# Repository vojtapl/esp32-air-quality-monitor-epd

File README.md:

<h1 align="center">
    
</h1>

# SEN66 Air Quality Monitor With EPD Output

The goal of this project is to create portable air quality monitor, which can be
used to measure the air quality in all environments I am in throughout the day,
especially where I sleep. Some sample measurements available
[here](/software/sample%20data/README.md).

## Readme if you Consider Making This

I would like make a new hardware and accompanying software revision, as I have
found some design quirks I have made:

- I have accidentally bought BWR EPD instead of the newer BWRY, forcing me to
  not be able to use the yellow color.
- The power button is sunken too much (by about 1 mm).
- The rotary encoder is not a good user interface, as the EPD has a refresh time
  of about 15 seconds (though the BWRY version may improve this); dedicated
  buttons would be better.
- The cable to the SEN66 sensor is quite finicky to make without the proper
  tools.
- Looking at the SEN66 sensor itself, it is of a very nice form factor, though
  not that good price-wise.

## To-Do:

- Add photos, features, and description.
- Beautify the code.
- Check the accuracy displayed.
- Record and add some data on Git.
- Clear display of current values with _badness level_.
- Show trend in overview.
- Consider adding AP functionality.
- Consider using bat_low alarm.
- Consider adding red background to really bad values.
- Add average overview.
- Optimize the power consumption.

### To-Do for Next Revision(s)

- Consider adding soft power button.
- Consider adding a _busy_ LED if the BWRY EPD still has slow update time.
- Create a version without battery.

## Build Instructions

### Required parts:

- 1x M3x(3-5) mm grub screw
- 3x M3x(15-25) mm screw with countersunk head
- 3x M3 thread inserts suitable for a 4 mm hole
- micro SD card for data storage and graphing function
- 0.5 mm plastic sheet cut to 37 mm x 73 mm as a protection for the EPD (though
  with a little modification to the case files can be disregarded)
- populated PCB with a cap for the power switch
- printed case, encoder knob and a gasket for SEN66 (recommended to be made with
  a flexible plastic; not required)
- SEN66 - PCB connection wire
- 18650 battery, if non-powered usage is desired

### Some Photos Which Should Help

<h3 align="center">
    
</h3>
<h3 align="center">
    
</h3>
<h3 align="center">
    
</h3>
<h3 align="center">
    
</h3>

## Air Quality Thresholds Table

|                                | PM2.5, PM1, PM4 | PM10       | humidex  | voc, nox index | CO2          |
| ------------------------------ | --------------- | ---------- | -------- | -------------- | ------------ |
| good                           | [0; 9]          | [0; 55]    | [0; 28]  | [0; 50]        | [400; 800]   |
| moderate                       | (9; 35.5]       | (55; 155]  | (28; 32] | (50; 100]      | (800; 1000]  |
| unhealthy for sensitive groups | (35.5; 55.5]    | (155; 255] | (32; 36] | (100; 200]     | (1000; 1500] |
| unhealthy                      | (55.5; 125.5]   | (255; 355] | (36; 42] | (200; 300]     | (1500; 2000] |
| very unhealhty                 | (125.5; 225.5]  | (355; 425] | (42; 45] | (300; 400]     | (2000; 5000] |
| hazardous                      | (225.5; ∞]      | (425; ∞]   | (45; ∞)  | (400; ∞)       | (5000; ∞)    |

Based on:

- [Agency for Toxic Substances and Disease Registry (ATSDR). 2024. Guidance for Inhalation Exposures to Particulate Matter. U.S. Department of Health and Human Services, Public Health Service, Atlanta, GA. June 2024 update, Appendix B](https://www.atsdr.cdc.gov/pha-guidance/resources/ATSDR-Particulate-Matter-Guidance-508.pdf)
  for PM2.5 (and from it PM1 and PM4 as there do not seem to be any specific
  resources for these) and PM10
- [XIRIS. "Environmental and Indoor Measuring." XIRIS, https://www.xiris.si/en/projects/environmental-and-indoor-measuring/. Accessed 1 Aug. 2025](https://www.xiris.si/en/projects/environmental-and-indoor-measuring/)
  for CO2 with lowered good and moderate levels
- [Environment and Climate Change Canada. (n.d.). Warm season weather hazards. Government of Canada. Retrieved August 1, 2025, from https://www.canada.ca/en/environment-climate-change/services/seasonal-weather-hazards/warm-season-weather-hazards.html#toc7](https://www.canada.ca/en/environment-climate-change/services/seasonal-weather-hazards/warm-season-weather-hazards.html#toc7)
  for humidex
- The VOC and NOX indices are not based on anything as I have not found any good
  interpretation help in SEN66's docs. From my measurements the NOX usually
  hovers in the range [0; 2] and VOC jumps semi randomly. I would like to
  investigate these values more in the future.

## Attributions

- The SD card, Wi-Fi and battery icons are made by Gaai available at
  [lopaka](https://github.com/sbrin/lopaka).
- The font used for the charging status markings on the case is Atkinson
  Hyperlegible, available at
  [Braille Institute's website](https://www.brailleinstitute.org/freefont/)
- The SD card abstraction functions are based on
  [this example](https://github.com/espressif/arduino-esp32/blob/master/libraries/SD_MMC/examples/SDMMC_Test/SDMMC_Test.ino).

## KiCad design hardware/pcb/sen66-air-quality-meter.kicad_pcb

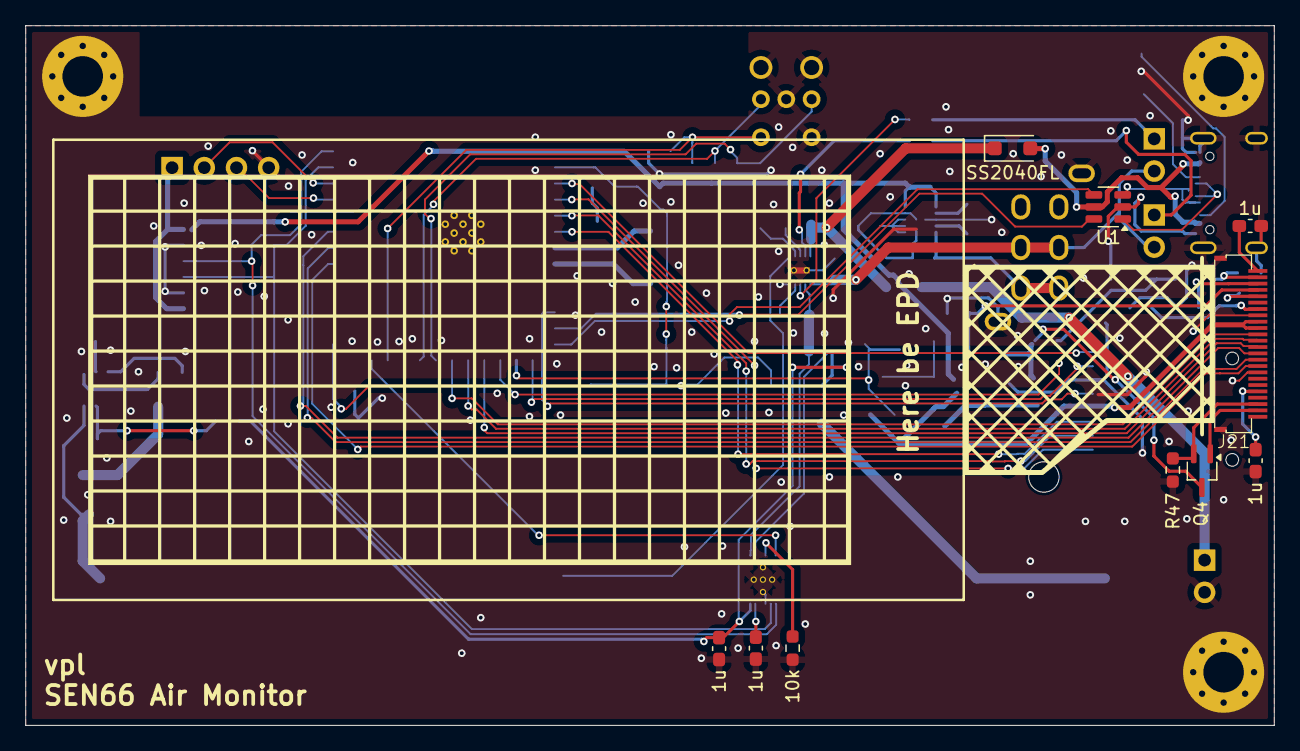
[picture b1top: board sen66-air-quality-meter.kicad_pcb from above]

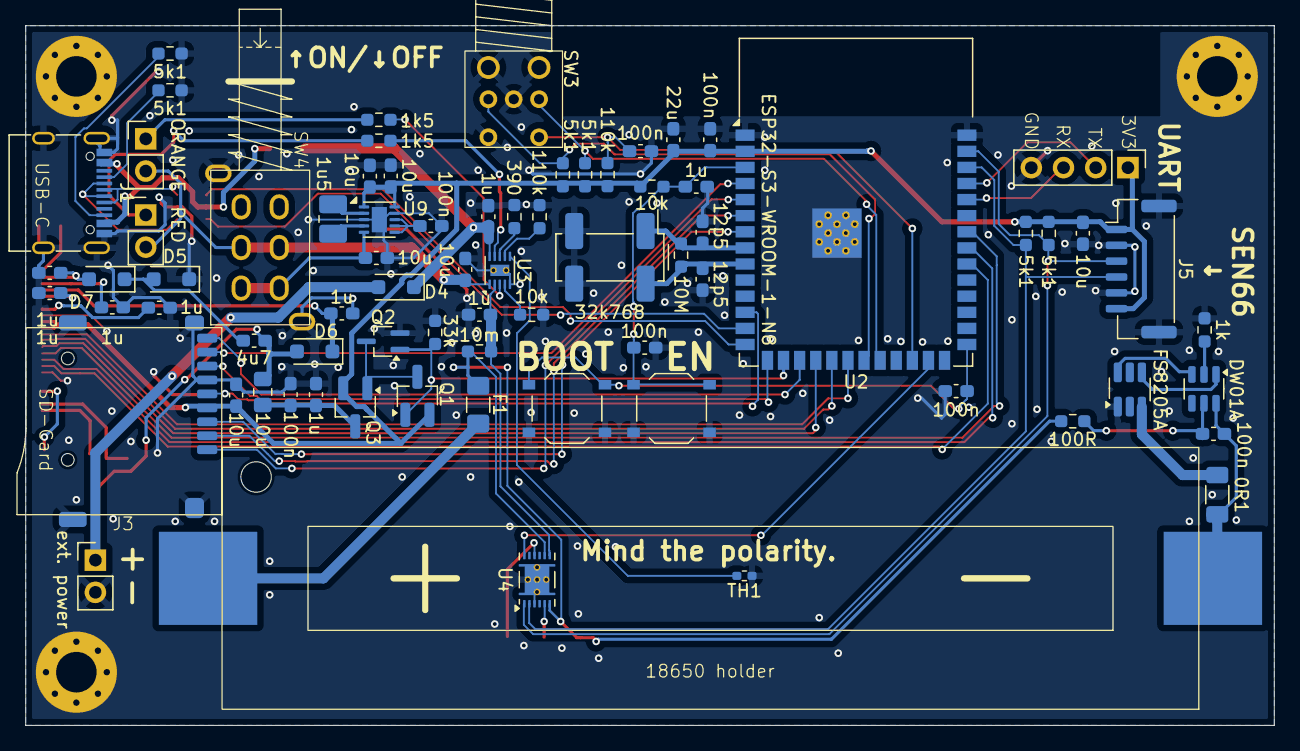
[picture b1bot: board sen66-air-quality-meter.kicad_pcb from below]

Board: 2 copper layers, 98.5 x 55.2 mm, 88 parts (75 on the bottom side), 74 nets.

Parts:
BT1: 18650 battery holder; BH-18650-B1BA002
C1, C2, C6, C8, C15, C26, C28: 100n; C_0603_1608Metric_Pad1.08x0.95mm_HandSolder
C3, C7, C10, C14, C16, C17, C19, C20, C21, C22, C23, C24, C25: 1u; C_0603_1608Metric_Pad1.08x0.95mm_HandSolder
C4, C5: 12p5; C_0603_1608Metric_Pad1.08x0.95mm_HandSolder
C9: 22u; C_0603_1608Metric_Pad1.08x0.95mm_HandSolder
C11, C12, C13, C27, C29, C30: 10u; C_0603_1608Metric_Pad1.08x0.95mm_HandSolder
C18: 4u7; C_0603_1608Metric_Pad1.08x0.95mm_HandSolder
D1: RED; PinHeader_1x02_P2.54mm_Vertical
D2: ORANGE; PinHeader_1x02_P2.54mm_Vertical
D3, D4, D5, D6, D7: SS2040FL; D_SOD-123F
F1: Polyfuse 2A; Fuse_1206_3216Metric_Pad1.42x1.75mm_HandSolder
H2, H3, H4: MountingHole_Pad; MountingHole_3.2mm_M3_Pad_Via
J1: USB-C female, 16P; USB_C_Receptacle_G-Switch_GT-USB-7010ASV
J2: ext. power; PinHeader_1x02_P2.54mm_Vertical
J3: SHOU HAN TF PUSH
J4: UART; PinHeader_1x04_P2.54mm_Vertical
J5: WAFER-GH1.25-6PLB; JST_GH_BM06B-GHS-TBT_1x06-1MP_P1.25mm_Vertical
J21: FH34SRJ24S; FH34SRJ-24S-0.5SH(50)
L1: 10u; L_0805_2012Metric_Pad1.15x1.40mm_HandSolder
L2: 1u5; L_1008_2520Metric_Pad1.43x2.20mm_HandSolder
Q1, Q3: AP2305; SOT-23_Handsoldering
Q2, Q4: SI1308EDL; SOT-323_SC-70_Handsoldering
R1, R2, R4, R5, R7, R8: 5k1; R_0603_1608Metric_Pad0.98x0.95mm_HandSolder
R3, R9, R16: 10k; R_0603_1608Metric_Pad0.98x0.95mm_HandSolder
R6, R11: 110k; R_0603_1608Metric_Pad0.98x0.95mm_HandSolder
R10: 10M; R_0603_1608Metric_Pad0.98x0.95mm_HandSolder
R12, R13: 1k5; R_0603_1608Metric_Pad0.98x0.95mm_HandSolder
R14: 390; R_0603_1608Metric_Pad0.98x0.95mm_HandSolder
R15: 33k; R_0603_1608Metric_Pad0.98x0.95mm_HandSolder
R17: 10m; R_0603_1608Metric_Pad0.98x0.95mm_HandSolder
R18: 1k; R_0603_1608Metric_Pad0.98x0.95mm_HandSolder
R19: R47; R_0603_1608Metric_Pad0.98x0.95mm_HandSolder
R20: 0R1; R_1206_3216Metric_Pad1.30x1.75mm_HandSolder
R21: 100R; R_0603_1608Metric_Pad0.98x0.95mm_HandSolder
SW1, SW2: TS-1187A; SW_Push_1P1T_XKB_TS-1187A
SW3: ED08905M; ED08905M-FE13C7.3-C10-2053
SW4: XKBS22E05-Z
TH1: NTCG104BH103HT1; R_0402_1005Metric_Pad0.72x0.64mm_HandSolder
U1: USBLC6-2SC6; SOT-23-6
U2: ESP32-S3-WROOM-1-N8; ESP32-S3-WROOM-1
U3: BQ25185; Texas_DLH0010A_WSON-10-1EP_2.2x2mm_P0.4mm_EP0.9x1.5mm_Therm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
U4: BQ27441DRZR-G1A; Texas_S-PDSO-N12
U6: DW01A; SOT-23-6
U7: FS8205A; SOT-23-6_Handsoldering
U9: TPS63031DSK; WSON-10-1EP_2.5x2.5mm_P0.5mm_EP1.2x2mm
Y1: 32k768; Crystal_SMD_SeikoEpson_MC306-4Pin_8.0x3.2mm_HandSoldering

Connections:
+3V3: C8.1, C9.1, C12.1, C13.1, C29.1, C30.1, J3.4 (VDD), J4.1, J5.1, J5.6, J21.15, J21.16, Q1.2 (S), Q3.2 (S), R1.1, R2.1, R3.1, R6.1, R7.1, R8.1, U2.2 (3V3), U9.1 (VOUT), U9.10 (FB)
/BOOT_OPTION: C2.1, SW2.1, U2.27 (IO0)
/BUSY: J21.9, U2.32 (IO39)
/D/C: J21.11, U2.34 (IO41)
/EN: C1.1, C3.2, R3.2, SW1.1, U2.3 (EN)
/EPD_POWER: Q1.1 (G), Q2.1 (G), R15.1, U2.16 (IO46)
/RES: J21.10, U2.33 (IO40)
/RX: J4.3, U2.36 (RXD0)
/SCL: J5.4, R8.2, U2.38 (IO2), U4.2 (SCL)
/SD CLK: J3.5 (CLK), U2.12 (IO8)
/SD CMD: J3.3 (CMD), U2.7 (IO7)
/SD D0: J3.7 (DAT0), U2.15 (IO3)
/SD D1: J3.8 (DAT1), U2.4 (IO4)
/SD D2: J3.1 (DAT2), U2.5 (IO5)
/SD D3: J3.2 (DAT3/CD), U2.6 (IO6)
/SD DET: J3.9 (DET), U2.17 (IO9)
/SDA: J5.3, R7.2, U2.39 (IO1), U4.1 (SDA)
/SPI_MOSI: J21.14, U2.20 (IO12)
/SPI_SCLK: J21.13, U2.19 (IO11)
/TX: J4.2, U2.37 (TXD0)
/USB 5V: D3.2 (A), J1.A4 (VBUS), J1.A9 (VBUS), J1.B4 (VBUS), J1.B9 (VBUS), U1.5 (VBUS)
/USB D+: U1.4 (I/O2), U2.14 (USB_D+)
/USB D-: U1.6 (I/O1), U2.13 (USB_D-)
/V_{BAT}: C10.1, R17.2, U3.2 (BAT), U4.7 (SRN)
/bat low alarm: U2.25 (IO48), U4.12 (GPOUT)
/encoder A: R2.2, SW3.A, U2.21 (IO13)
/encoder B: R1.2, SW3.B, U2.22 (IO14)
/encoder button: C6.2, R6.2, SW3.S1, U2.24 (IO47)
/~SPI_EPD_CS: J21.12, U2.18 (IO10)
GND: C1.2, C2.2, C3.1, C4.2, C5.2, C6.1, C7.2, C8.2, C9.2, C10.2, C11.2, C12.2, C13.2, C14.2, C15.2, C16.2, C17.2, C19.2, C20.2, C21.2, C22.2, C23.2, C24.2, C25.2, C27.2, C28.2, C29.2, C30.2, D5.1 (K), H2.1, H3.1, H4.1, J1.A1 (GND), J1.A12 (GND), J1.B1 (GND), J1.B12 (GND), J1.S1 (SHIELD), J2.2, J3.6 (VSS), J3.10 (SHIELD), J4.4, J5.2, J5.5, J5.MP (MountPin), J21.8, J21.17, J21.MP (MountPin), Q2.2 (S), R4.2, R5.2, R9.1, R11.2, R14.2, R15.2, R16.1, R18.2, R19.2, SW1.2, SW2.2, SW3.C, SW3.MP, SW3.S2, SW4.MP, TH1.1, U1.2 (GND), U2.1 (GND), U2.40 (GND), U2.41 (GND), U3.5 (GND), U3.11 (Thermal_Pad), U4.3 (V_{SS}), U4.13 (PAD), U7.1 (S1), U9.3 (PGND), U9.9 (GND), U9.11 (PGND), Y1.2, Y1.3
unnamed: BT1.1 (+), F1.2
unnamed: BT1.2 (-), C26.2, R20.2, U6.6 (GND)
unnamed: D1.1 (K), R12.1
unnamed: D2.1 (K), R13.1
unnamed: C7.1, D3.1 (K), D4.1 (K), U3.10 (IN)
unnamed: D4.2 (A), J2.1
unnamed: C18.2, D5.2 (A), D7.1 (K)
unnamed: C18.1, D6.2 (A), L1.2, Q4.3 (D)
unnamed: C19.1, D6.1 (K), J21.21
unnamed: C20.1, D7.2 (A), J21.23
unnamed: J1.A5 (CC1), R4.1
unnamed: J1.B5 (CC2), R5.1
unnamed: J1.A6 (D+), J1.B6 (D+), U1.3 (I/O2)
unnamed: J1.A7 (D-), J1.B7 (D-), U1.1 (I/O1)
unnamed: J21.2, Q4.1 (G)
unnamed: J21.3, Q4.2 (S), R19.1
unnamed: C21.1, J21.5
unnamed: C22.1, J21.18
unnamed: C23.1, J21.20
unnamed: C24.1, J21.22
unnamed: C25.1, J21.24
unnamed: Q1.3 (D), Q2.3 (D), Q3.1 (G)
unnamed: C15.1, C16.1, L1.1, Q3.3 (D)
unnamed: C4.1, R10.1, U2.8 (IO15), Y1.1
unnamed: C5.1, R10.2, U2.9 (IO16), Y1.4
unnamed: R11.1, U3.7 (ILIM/VSET)
unnamed: R14.1, U3.8 (I_{SET})
unnamed: R12.2, U3.9 (STAT1)
unnamed: R13.2, U3.3 (STAT2)
unnamed: TH1.2, U3.6 (TS/MR)
unnamed: R9.2, U3.4 (~CE)
unnamed: C17.1, F1.1, R17.1, R21.1, U4.6 (BAT), U4.8 (SRP)
unnamed: R16.2, U4.10 (BIN)
unnamed: C14.1, U4.5 (V_{DD})
unnamed: R18.1, U6.2 (CS)
unnamed: U6.3 (OC), U7.6 (G1)
unnamed: U6.1 (OD), U7.4 (G2)
unnamed: C26.1, R21.2, U6.5 (VCC)
unnamed: R20.1, U7.3 (S2)
unnamed: C28.1, U9.6 (EN), U9.7 (PS/SYNC), U9.8 (VINA)
unnamed: L2.2, U9.4 (L1)
unnamed: L2.1, U9.2 (L2)
unnamed: C27.1, SW4.3, SW4.6, U9.5 (VIN)
VBUS: C11.1, D1.2 (A), D2.2 (A), SW4.2, SW4.5, U3.1 (SYS)

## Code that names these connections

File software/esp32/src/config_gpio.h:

// GPIO ping definitions
#pragma once
#include <PDLS_EXT3_Basic_Global.h>

// UART
#define UART_TX 37
#define UART_RX 36

// I2C
#define I2C_SDA 1
#define I2C_SCL 2

// SD card
#define D0 3
#define D1 4
#define D2 5
#define D3 6
#define CMD 7
#define CLK 8
#define SD_DET 9

// EPD + SPI
#define NSPI_EDP_CS 10
#define SPI_SCLK 11
#define SPI_MOSI 12
#define EPD_BUSY 39
#define EPD_RES 40
#define EPD_D_C 41
#define EPD_POWER 46

// rotary encoder
#define ROTARY_ENCODER_A 13
#define ROTARY_ENCODER_B 14
#define ROTARY_ENCODER_BTN 47

// other
#define ALARM_LOW_BAT 48

pins_t epd_pins = {
    .panelBusy = EPD_BUSY,
    .panelDC = EPD_D_C,
    .panelReset = EPD_RES,
    .flashCS = NOT_CONNECTED,
    .panelCS = NSPI_EDP_CS,
    .panelCSS = NOT_CONNECTED,
    .flashCSS = NOT_CONNECTED,
    .panelPower = EPD_POWER,
};

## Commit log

2025-08-02 Initial commit.
2025-08-05 added license
2025-08-05 update acknowledgements, added some assembly info
2025-08-05 graph - add seeking to relevant part; fix typo
2025-08-11 add more data
2025-08-11 relative -> absolute img adresses
